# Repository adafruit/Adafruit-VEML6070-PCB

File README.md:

## Adafruit VEML6070 Sensor PCB
<a href="http://www.adafruit.com/products/2899"><br/>
Click here to purchase one from the Adafruit shop</a>

This little sensor is a great way to add UV light sensing to any microcontroller project. The VEML6070 from Vishay has a true UV A light sensor and an I2C-controlled ADC that will take readings and integrate them for you over ~60ms to 500ms.

Please note, for UV sensing we now recommend the VEML6075 which is an improved version of this sensor with both UVA and UVB sensors and UV Index calculations

Unlike the Si1145, this sensor will not give you UV Index readings. However, the Si1145 does UV Index approximations based on light level not true UV sensing. The VEML6070 in contrast does have a real light sensor in the UV spectrum. It's also got a much much simpler I2C interface so you can run it on the smallest microcontrollers with ease. Unlike the GUVA analog sensor, the biasing and ADC is all internal so you don't need an ADC.

This UV sensor works great with 3 or 5V power or logic, its nice and compact, and its easy to use with any I2C-capable microcontroller. Each order comes with one assembled PCB with a sensor, some handy pullup resistors, a 270K rset resistor and a small piece of header. Some light soldering is required to attach the header but its a fast task!

PCB files for Adafruit VEML6070 sensor breakout. The format is EagleCAD schematic and board layout
- https://www.adafruit.com/product/2899

### License

Adafruit invests time and resources providing this open source design, please support Adafruit and open-source hardware by purchasing products from [Adafruit](https://www.adafruit.com)!

All text above must be included in any redistribution

Designed by Limor Fried/Ladyada for Adafruit Industries.
Creative Commons Attribution/Share-Alike, all text above must be included in any redistribution. 
See license.txt for additional information.

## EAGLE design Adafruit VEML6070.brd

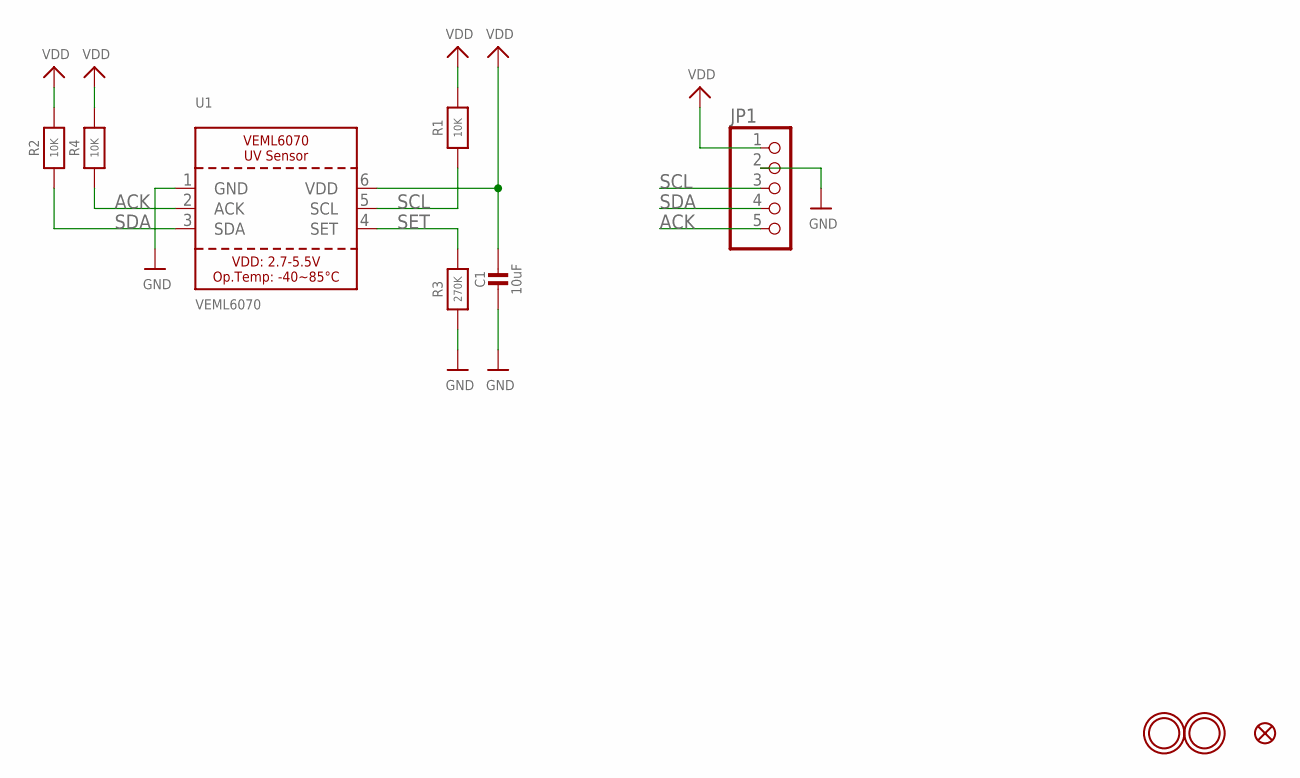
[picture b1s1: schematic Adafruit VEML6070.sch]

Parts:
C1: 10uF; 0805-NO
FID1: FIDUCIAL""; FIDUCIAL_1MM
JP1: HEADER-1X570MIL; 1X05_ROUND_70
R1, R2, R4: 10K; 0805-NO
R3: 270K; 0805-NO
U1: VEML6070
U$10, U$11: MOUNTINGHOLE2.5; MOUNTINGHOLE_2.5_PLATED

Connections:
ACK: JP1.5, R4.1, U1.2 (ACK)
GND: C1.2, JP1.2, R3.1, U1.1 (GND)
SCL: JP1.3, R1.1, U1.5 (SCL)
SDA: JP1.4, R2.1, U1.3 (SDA)
SET: R3.2, U1.4 (SET)
VDD: C1.1, JP1.1, R1.2, R2.2, R4.2, U1.6 (VDD)

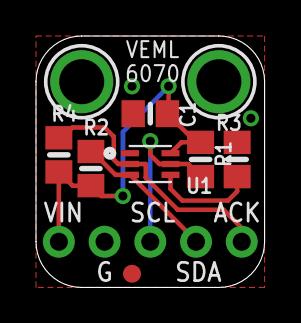
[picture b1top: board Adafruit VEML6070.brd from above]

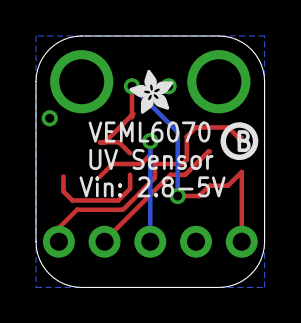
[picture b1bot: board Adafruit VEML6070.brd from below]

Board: 2 copper layers, 12.7 x 14.0 mm, 12 parts (2 on the bottom side), 6 nets.

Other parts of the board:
U$2: PCBFEAT-REV-040
U$14: ADAFRUIT_2.5MM

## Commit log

2016-05-16 init

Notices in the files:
parts and their libraries:
microbuilder: This work is placed in the public domain, and may be freely used for commercial and non-commercial work with the following conditions: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
